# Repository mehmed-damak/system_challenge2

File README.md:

# SafeShift
SafeShift is a system meant to be retrofitted on new and/or old industrial vehicles. The Goal of Safeshift is to provide assistance in preventative maintenance and in safety (and limited power tracking to where it applies). SafeShift is meant to be modular and be a plug and play module, that can work on any vehicle both new and old.

## Physical Installation
The main SafeShift board is to be placed in space inside the drivers cabin. and the sensors respective connectors will be plugged into them. The sensors are to be bolted/fasted to their repective areas (defined below). _NOTE: not ALL sensors must be connected to use SafeShift_

## Connectivity and Dashboard
The Preventative Maintenance Part of the systam connects to a dashboard through wifi or bluetooth, and provides sensor reading, both past and present. A simple learning model from previous data shows the current status of the system based on the data gathered. 

## Safety 
SafeShift uses a combination of sensors to ensure real-time safety monitoring and intelligent decision-making in industrial vehicles. It integrates JSN-SR04T (ultrasonic sensor) for proximity and obstacle detection, RCWL-0516 (microwave radar sensor) for motion detection, ADXL345 (MEMS accelerometer) for vibration and tilt monitoring, DS18B20 (digital temperature sensor) for thermal monitoring, WCS1500 (Hall-effect current sensor) for system current measurement, and A3144 (Hall-effect sensor) for position and magnetic detection. These sensors enable features such as blind spot detection, pedestrian awareness, and environment-adaptive responses in dynamic industrial settings. Together, this multi-sensor approach provides reliable, low-cost, and scalable safety coverage, significantly improving operational safety and system awareness.

## Preventative Maintenance
SafeShift tracks the following parameters in Industrial Vehicles: Vibration in motor pumps, temperature of motor-pumps. it uses a simple DS18B20 to track temperature sensors and an ADXL345 for vibrations. There are 4 of each applicable to this system.

## Energy Tracking 
If the vehicle is equipped with an electrical system, consumption is monitored via real-time current data shown on the dashboard through the current sensor.
Note: The voltage is to be set by the user following the vehicles specifications.

## Usage
SafeShift is designed for simple and intuitive usage, requiring the operator to download and launch the mobile application and connect to the system via WiFi or Bluetooth.

run app

Once connected, the dashboard provides real-time monitoring of vehicle status and safety conditions.

If proximity is detected, a buzzer alarm is activated. 
If a pedestrian is detected, a buzzer alarm is also triggered. 
If the seatbelt is not fastened, an LED indicator is activated. 
If the door is not properly closed, an LED indicator is turned on. 
If the load is too heavy, a pressure LED is activated.

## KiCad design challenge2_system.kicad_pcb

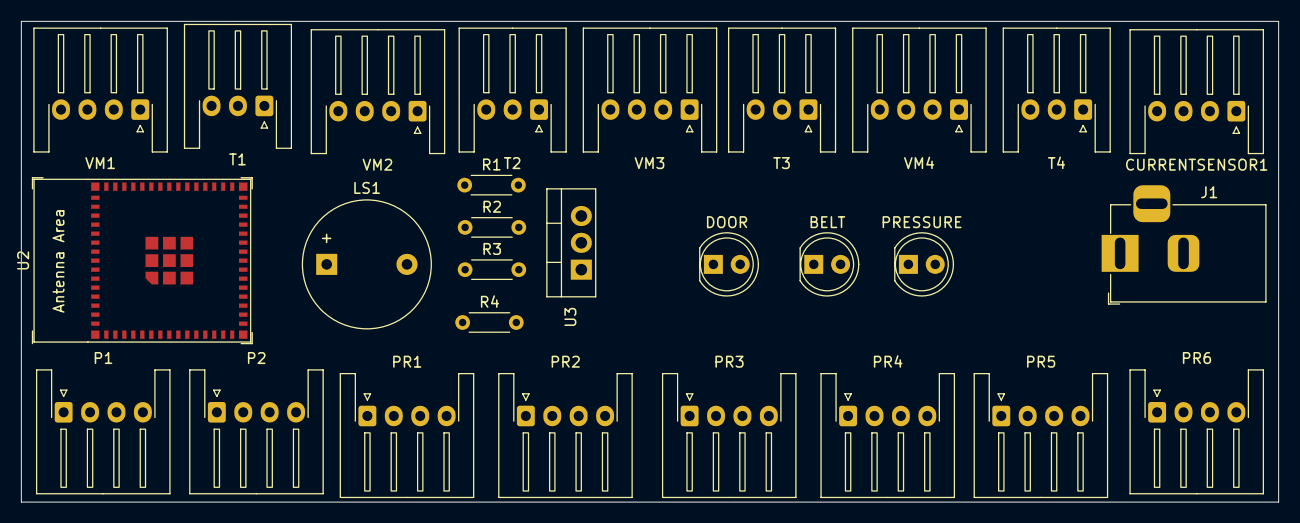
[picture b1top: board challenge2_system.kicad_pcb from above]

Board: 2 copper layers, 119.0 x 45.5 mm, 28 parts (0 on the bottom side), 40 nets, no tracks yet.

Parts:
BELT: LED; LED_D5.0mm
CURRENTSENSOR1: Conn_01x04_Pin; JST_XH_S4B-XH-A-1_1x04_P2.50mm_Horizontal
DOOR: LED; LED_D5.0mm
J1: Barrel_Jack_Switch_Pin3Ring; BarrelJack_Horizontal
LS1: Speaker; Buzzer_12x9.5RM7.6
P1, P2: Conn_01x04_Pin; JST_XH_S4B-XH-A-1_1x04_P2.50mm_Horizontal
PR1, PR2, PR3, PR4, PR5, PR6: Conn_01x04_Pin; JST_XH_S4B-XH-A-1_1x04_P2.50mm_Horizontal
PRESSURE: LED; LED_D5.0mm
R1, R2, R3, R4: R; R_Axial_DIN0204_L3.6mm_D1.6mm_P5.08mm_Horizontal
T1, T2, T3, T4: Conn_01x03_Pin; JST_XH_S3B-XH-A-1_1x03_P2.50mm_Horizontal
U2: ESP32-S3-MINI-1
U3: LD1117V33; TO-220-3_Vertical
VM1, VM2, VM3, VM4: Conn_01x04_Pin; JST_XH_S4B-XH-A-1_1x04_P2.50mm_Horizontal

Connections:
+3V3: CURRENTSENSOR1.4, P1.1, P2.1, PR1.1, PR2.1, PR3.1, PR4.1, PR5.1, PR6.1, T1.1, T2.1, T3.1, T4.1, U3.2 (VO), VM1.3, VM2.3, VM3.3, VM4.3
/PIN A1: P1.3, U2.20 (GPIO16/U0CTS/ADC2_CH5/XTAL_32K_N)
/PINA2: P2.3, U2.24 (GPIO20/U1CTS/ADC2_CH9/CLK_OUT1/USB_D+)
/PINB1: P1.4, U2.19 (GPIO15/U0RTS/ADC2_CH4/XTAL_32K_P)
/PINB2: P2.4, U2.23 (GPIO19/U1RTS/ADC2_CH8/CLK_OUT2/USB_D-)
GND: BELT.1 (K), CURRENTSENSOR1.1, DOOR.1 (K), J1.3, LS1.1, P1.2, P2.2, PR1.4, PR2.4, PR3.4, PR4.4, PR5.4, PR6.4, PRESSURE.1 (K), T1.3, T2.3, T3.3, T4.3, U2.1 (GND), U2.2 (GND), U2.42 (GND), U2.43 (GND), U2.46 (GND), U2.47 (GND), U2.48 (GND), U2.49 (GND), U2.50 (GND), U2.51 (GND), U2.52 (GND), U2.53 (GND), U2.54 (GND), U2.55 (GND), U2.56 (GND), U2.57 (GND), U2.58 (GND), U2.59 (GND), U2.60 (GND), U2.61 (GND), U2.62 (GND), U2.63 (GND), U2.64 (GND), U2.65 (GND), U3.1 (GND), VM1.4, VM2.4, VM3.4, VM4.4
unnamed: CURRENTSENSOR1.3, U2.25 (GPIO21)
unnamed: DOOR.2 (A), R1.1
unnamed: BELT.2 (A), R2.1
unnamed: PRESSURE.2 (A), R4.1
unnamed: LS1.2, R3.2
unnamed: PR1.2, U2.35 (MTCK/GPIO39/CLK_OUT3/SUBSPICS1)
unnamed: PR1.3, U2.36 (MTDO/GPIO40/CLK_OUT2)
unnamed: PR2.2, U2.37 (MTDI/GPIO41/CLK_OUT1)
unnamed: PR2.3, U2.38 (MTMS/GPIO42)
unnamed: PR3.2, U2.26 (GPIO26)
unnamed: PR3.3, U2.28 (SPIIO4/GPIO33/FSPIHD/SUBSPIHD)
unnamed: PR4.2, U2.29 (SPIIO5/GPIO34/FSPICS0/SUBSPICS0)
unnamed: PR4.3, U2.31 (SPIIO6/GPIO35/FSPID/SUBSPID)
unnamed: PR5.2, U2.32 (SPIIO7/GPIO36/FSPICLK/SUBSPICLK)
unnamed: PR5.3, U2.33 (SPIDQS/GPIO37/FSPIQ/SUBSPIQ)
unnamed: PR6.2, U2.27 (GPIO47/SPICLK_P/SUBSPICLK_P_DIFF)
unnamed: PR6.3, U2.44 (GPIO46)
unnamed: T1.2, U2.10 (GPIO6/TOUCH6/ADC1_CH5)
unnamed: T2.2, U2.13 (GPIO9/TOUCH9/ADC1_CH8/FSPIHD/SUBSPIHD)
unnamed: T3.2, U2.21 (GPIO17/U1TXD/ADC2_CH6)
unnamed: T4.2, U2.16 (GPIO12/TOUCH12/ADC2_CH1/FSPICLK/FSPIIO6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)
unnamed: R3.1, U2.4 (GPIO0/BOOT)
unnamed: R2.2, U2.5 (GPIO1/TOUCH1/ADC1_CH0)
unnamed: R1.2, U2.6 (GPIO2/TOUCH2/ADC1_CH1)
unnamed: U2.8 (GPIO4/TOUCH4/ADC1_CH3), VM1.2
unnamed: U2.9 (GPIO5/TOUCH5/ADC1_CH4), VM1.1
unnamed: U2.11 (GPIO7/TOUCH7/ADC1_CH6), VM2.2
unnamed: U2.12 (GPIO8/TOUCH8/ADC1_CH7/SUBSPICS1), VM2.1
unnamed: U2.14 (GPIO10/TOUCH10/ADC1_CH9/FSPICS0/FSPIIO4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), VM4.2
unnamed: U2.15 (GPIO11/TOUCH11/ADC2_CH0/FSPID/FSPIIO5/S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), VM4.1
unnamed: U2.17 (GPIO13/TOUCH13/ADC2_CH2/FSPIQ/FSPIIO7/S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), VM3.2
unnamed: U2.18 (GPIO14/TOUCH14/ADC2_CH3/FSPIWP/FSPIDQS/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), VM3.1
unnamed: R4.2, U2.39 (U0TXD/GPIO43/CLK_OUT1)
unnamed: J1.1, U3.3 (VI)

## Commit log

2026-04-05 spelling
2026-04-05 add intro and pierwsze subsection
2026-04-05 add pcb circuit diagram
2026-04-05 start c and d
2026-04-05 Enhance README with Safety and Maintenance sections
    Added sections on Safety and Preventative Maintenance to README.
2026-04-05 Add Safety
2026-04-05 Update README with preventative maintenance details
    Added details about parameters tracked for preventative maintenance.
2026-04-05 Update README with improved preventative maintenance details
    Clarified the description of preventative maintenance parameters and corrected the sentence structure.
2026-04-05 add img
2026-04-05 Update README with images and typo corrections
    Added images and corrected typos in the README.
2026-04-05 Expand README with usage and safety feature details
    Added usage instructions and safety features for SafeShift.
